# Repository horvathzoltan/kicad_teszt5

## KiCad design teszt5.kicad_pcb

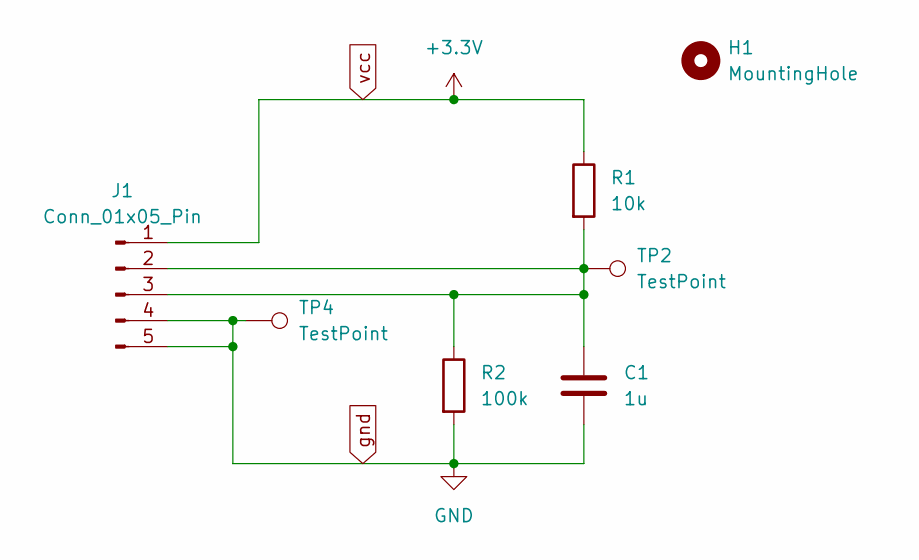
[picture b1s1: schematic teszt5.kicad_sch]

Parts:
C1: 1u; C_1206_3216Metric_Pad1.33x1.80mm_HandSolder
H1: MountingHole; MountingHole_3.2mm_M3_ISO14580
J1: Conn_01x05_Pin; PinHeader_1x05_P2.54mm_Vertical_SMD_Pin1Left
R1: 10k; R_1206_3216Metric_Pad1.30x1.75mm_HandSolder
R2: 100k; R_1206_3216Metric_Pad1.30x1.75mm_HandSolder
TP2, TP4: TestPoint; TestPoint_Pad_1.0x1.0mm

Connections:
unnamed: C1.1, J1.2, J1.3, R1.2, R2.1, TP2.1
gnd: C1.2, J1.4, J1.5, R2.2, TP4.1
vcc: J1.1, R1.1

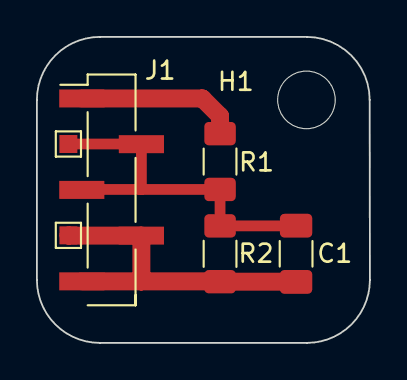
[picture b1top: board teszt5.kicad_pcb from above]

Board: 2 copper layers, 18.5 x 17.0 mm, 7 parts (0 on the bottom side), 3 nets.
